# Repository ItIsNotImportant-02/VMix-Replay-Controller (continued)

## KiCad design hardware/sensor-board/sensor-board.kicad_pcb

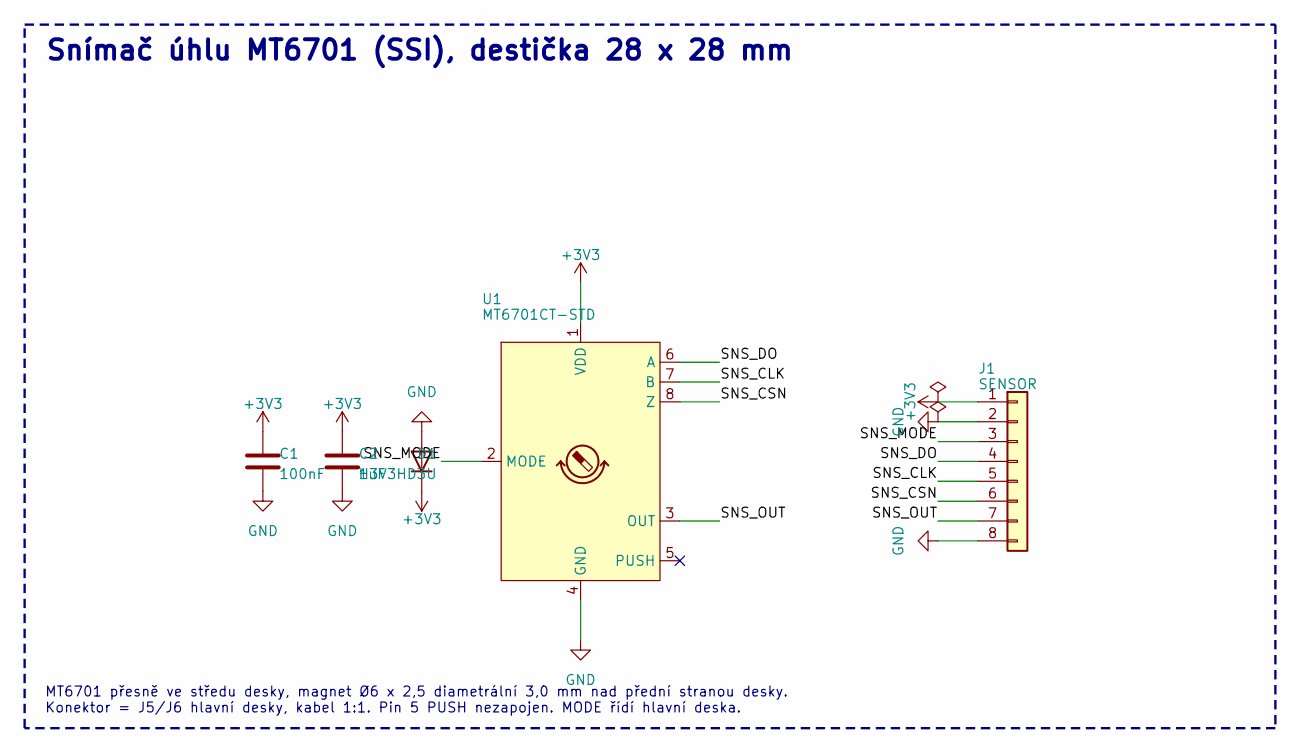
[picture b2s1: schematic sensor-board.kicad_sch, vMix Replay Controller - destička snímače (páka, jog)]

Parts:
C1: 100nF; C_0603_1608Metric; LCSC C14663
C2: 1uF; C_0603_1608Metric; LCSC C15849
D1: H3V3HD3U; D_SOD-323; MPN hongjiacheng H3V3HD3U; LCSC C20615801
J1: SENSOR; JST_PH_S8B-PH-K_1x08_P2.00mm_Horizontal; MPN S8B-PH-K-S
U1: MT6701CT-STD; SOIC-8_3.9x4.9mm_P1.27mm; MPN MT6701CT-STD-R; LCSC C3003196

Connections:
+3V3: C1.1, C2.1, D1.1 (K), J1.1, U1.1 (VDD)
/SNS_CLK: J1.5, U1.7 (B)
/SNS_CSN: J1.6, U1.8 (Z)
/SNS_DO: J1.4, U1.6 (A)
/SNS_MODE: J1.3, U1.2 (MODE)
/SNS_OUT: J1.7, U1.3 (OUT)
GND: C1.2, C2.2, D1.2 (A), J1.2, J1.8, U1.4 (GND)

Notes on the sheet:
Snímač úhlu MT6701 (SSI), destička 28 x 28 mm
MT6701 přesně ve středu desky, magnet Ø6 x 2,5 diametrální 3,0 mm nad přední stranou desky. Konektor = J5/J6 hlavní desky, kabel 1:1. Pin 5 PUSH nezapojen. MODE řídí hlavní deska.

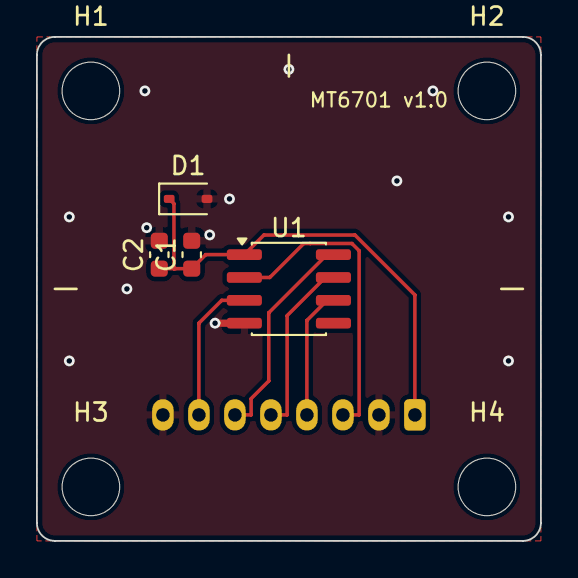
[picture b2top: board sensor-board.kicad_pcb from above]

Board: 2 copper layers, 28.0 x 28.0 mm, 9 parts (1 on the bottom side), 7 nets.

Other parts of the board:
H1, H2, H3, H4: MountingHole_3.2mm_M3

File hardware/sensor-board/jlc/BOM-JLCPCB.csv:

Comment,Designator,Footprint,LCSC Part #
100nF,C1,C_0603_1608Metric,C14663
1uF,C2,C_0603_1608Metric,C15849
H3V3HD3U,D1,D_SOD-323,C20615801
MT6701CT-STD,U1,SOIC-8_3.9x4.9mm_P1.27mm,C3003196

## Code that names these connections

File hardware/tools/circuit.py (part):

"""vMix Replay Controller main board: netlist description.

Run gen.py to turn this into KiCad schematic files. Pin assignment and design
notes are in hardware/DESIGN.md; keep both in sync.
"""
from schgen import Part
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    s.add(R("R2", "5.1k", "USB_CC2", "GND"))
    # SRV05-4 (Preferred, bez poplatku) místo USBLC6-2SC6: stejné pouzdro, 4 nezávislé diody, každá datová linka má 2
    s.add(Part("U1", "Power_Protection:SRV05-4", "SRV05-4", "Package_TO_SOT_SMD:SOT-23-6",
               pins={"1": "USB_CONN_DP", "4": "USB_CONN_DP", "3": "USB_CONN_DM", "6": "USB_CONN_DM",
                     "5": "VBUS", "2": "GND"}, lcsc="C7420376", mpn="hongjiacheng SRV05-4"))
    s.add(R("R3", "27R", "USB_CONN_DP", "USB_DP"))
    s.add(R("R4", "27R", "USB_CONN_DM", "USB_DM"))
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    # ABM8-272-T3 (doporučený v Hardware design with RP2040) má JLC skladem 1 ks (12. 11. 2026) -> náhrada se stejnou
    # zatěžovací kapacitou 10 pF, takže obvod (2x 15 pF + 1k) zůstává; ESR max 60 R místo 50 R.
    s.add(Part("Y1", "Device:Crystal_GND24", "12MHz", "Crystal:Crystal_SMD_3225-4Pin_3.2x2.5mm",
               pins={"1": "XIN", "3": "XTAL_OUT", "2": "GND", "4": "GND"}, lcsc="C5310728", mpn="TX322512M4DBDE2T",
               desc="Yajingxin 12 MHz, CL 10 pF, ESR max 60R, +-10 ppm, -30..85 C; pady 1 a 3 krystal, 2 a 4 GND"))
    s.add(R("R10", "1k", "XOUT", "XTAL_OUT"))
    s.add(C("C%d" % n, "15pF", "XIN")); n += 1      # CL 10 pF: 15/2 + ~3 pF parazitní = 10,5 pF (C0G)
    s.add(C("C%d" % n, "15pF", "XTAL_OUT")); n += 1
    s.add(Part("U4", "Memory_Flash:W25Q128JVS", "W25Q128JVSIQ", "Package_SO:SOIC-8_5.3x5.3mm_P1.27mm",
               pins={"1": "QSPI_SS", "2": "QSPI_SD1", "3": "QSPI_SD2", "4": "GND", "5": "QSPI_SD0",
                     "6": "QSPI_SCLK", "7": "QSPI_SD3", "8": "+3V3"}, lcsc="C97521"))
    s.add(C("C%d" % n, "100nF", "+3V3")); n += 1
    s.add(R("R11", "1k", "QSPI_SS", "BOOTSEL"))
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               pins={"1": "BOOTSEL", "2": "GND"}, lcsc="C318884"))
    s.add(R("R12", "10k", "+3V3", "RUN"))
    s.add(Part("SW2", "Switch:SW_Push", "RESET", "Button_Switch_SMD:SW_Push_1P1T_XKB_TS-1187A",
               pins={"1": "RUN", "2": "GND"}, lcsc="C318884"))
    s.add(R("R13", "1k", "STATUS_LED", "STATUS_LED_A"))   # žlutá Vf ~2 V -> ~1,3 mA
    s.add(Part("D3", "Device:LED", "yellow", LED0603, pins={"A": "STATUS_LED_A", "K": "GND"}, lcsc="C89811",
               mpn="NationStar NCD0603Y2"))
    s.add(Part("J2", "Connector_Generic:Conn_01x07", "DEBUG", "Connector_PinHeader_2.54mm:PinHeader_1x07_P2.54mm_Vertical",
               pins={"1": "+3V3", "2": "SWCLK", "3": "SWDIO", "4": "GND", "5": "RUN", "6": "UART_TX", "7": "UART_RX"},
               in_bom=False, desc="SWD + UART debug header (osadit ručně jen při ladění)"))
    exp = {"1": "+5V", "2": "+3V3", "3": "GND", "4": "GND", "5": "GP10", "6": "GP11", "7": "GP2", "8": "GP3",
           "9": "GP4", "10": "GP28", "15": "I2C_SDA", "16": "I2C_SCL"}
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    s = prj.sheet("Ethernet", "ethernet.kicad_sch", "W5500 + RJ45 HR911105A")
    s.note("Analogová část podle referenčního zapojení WIZnet W5500 (33R série, 49,9R terminace, 6,8nF na RX).")
    s.add(Part("U5", "Interface_Ethernet:W5500", "W5500", "Package_QFP:LQFP-48_7x7mm_P0.5mm",
               pins={"AVDD": "+3V3A", "AGND": "GND", "VDD": "+3V3", "GND": "GND", "TXN": "W_TXN", "TXP": "W_TXP",
                     "RXN": "W_RXN", "RXP": "W_RXP", "EXRES1": "W_EXRES", "VBG": None, "TOCAP": "W_TOCAP",
                     "1V2O": "W_1V2O", "RSVD": "GND", "SPDLED": None, "LINKLED": "W_LINKLED", "DUPLED": None,
                     "ACTLED": "W_ACTLED", "XI/CLKIN": "W_XI", "XO": "W_XO", "~{SCS}": "ETH_CS", "SCLK": "ETH_SCK",
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    for i in range(6):
        s.add(C("C%d" % n, "100nF", "+3V3A")); n += 1
    s.add(C("C%d" % n, "100nF", "+3V3")); n += 1
    s.add(C("C%d" % n, "4.7uF", "W_TOCAP")); n += 1
    s.add(C("C%d" % n, "10nF", "W_1V2O")); n += 1
    # EXRES1 12,4k 1 % (Basic neexistuje) = 10k + 2,4k v sérii, obě Basic 1 %
    s.add(R("R20", "10k", "W_EXRES", "W_EXRES_B"))
    s.add(R("R36", "2.4k", "W_EXRES_B", "GND"))
    s.add(Part("Y2", "Device:Crystal_GND24", "25MHz", "Crystal:Crystal_SMD_3225-4Pin_3.2x2.5mm",
               pins={"1": "W_XI", "3": "W_XO", "2": "GND", "4": "GND"}, lcsc="C9006", mpn="X322525MOB4SI (CL 12 pF)"))
    s.add(C("C%d" % n, "18pF", "W_XI")); n += 1    # CL 12 pF: 18/2 + ~3 pF = 12 pF (jako WIZ850io)
    s.add(C("C%d" % n, "18pF", "W_XO")); n += 1
    s.add(R("R21", "1M", "W_XI", "W_XO"))
    s.add(R("R22", "10k", "+3V3", "ETH_INT"))
    s.add(R("R23", "10k", "+3V3", "ETH_RST"))
    s.add(R("R35", "10k", "+3V3", "ETH_CS"))   # W5500 odpojený od SPI, dokud RP2040 nenastaví GPIO
    # TX
    s.add(R("R24", "0R", "W_TXP", "ETH_TDP"))
    s.add(R("R25", "0R", "W_TXN", "ETH_TDN"))
    s.add(R("R26", "49.9R 1%", "ETH_TDP", "+3V3A"))
    s.add(R("R27", "49.9R 1%", "ETH_TDN", "+3V3A"))
    s.add(R("R28", "10R", "+3V3A", "ETH_TCT"))
    s.add(C("C%d" % n, "22nF", "ETH_TCT")); n += 1
    # RX
    s.add(R("R29", "0R", "W_RXP", "ETH_RXP_T"))
    s.add(R("R30", "0R", "W_RXN", "ETH_RXN_T"))
    s.add(R("R31", "49.9R 1%", "ETH_RXP_T", "ETH_RCT"))
    s.add(R("R32", "49.9R 1%", "ETH_RXN_T", "ETH_RCT"))
    s.add(C("C%d" % n, "6.8nF", "ETH_RXP_T", "ETH_RDP")); n += 1
    s.add(C("C%d" % n, "6.8nF", "ETH_RXN_T", "ETH_RDN")); n += 1
    s.add(C("C%d" % n, "10nF", "ETH_RCT")); n += 1
    s.add(C("C56", "10uF", "+3V3"))   # bulk u VDD W5500 (reference WIZnet má 2x 10 uF)
    # LEDs
    # LED anody 12 a 9 na +3V3, katody 11 a 10 přes 330R do W5500 (aktivní v nule, max. 8 mA)
    s.add(R("R33", "330R", "W_LINKLED", "ETH_LINK_K"))
    s.add(R("R34", "330R", "W_ACTLED", "ETH_ACT_K"))
    s.add(Part("J4", "Connector:RJ45_Hanrun_HR911105A_Horizontal", "HR911105A", "Connector_RJ:RJ45_Hanrun_HR911105A_Horizontal",
               pins={"1": "ETH_TDP", "2": "ETH_TDN", "3": "ETH_RDP", "4": "ETH_TCT", "5": "ETH_RCT", "6": "ETH_RDN",
                     "8": "GND", "9": "+3V3", "10": "ETH_ACT_K", "11": "ETH_LINK_K", "12": "+3V3", "SH": "GND"},
               lcsc="C12074", in_bom=False, fields={"Assembly": "ruční pájení"}))
    prj.flag("+3V3A", s.name)
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    s.note("I_MAX = 58,5 x 1,3 V / R_EXT = 16,2 mA pro R_EXT 4,7k. Jas a celkový odběr omezuje firmware.\n"
           "U6 adresa 0x3C (AD=GND), U7 0x3F (AD=VCC). SDB stažený do nuly: LED po startu zhasnuté.")
    for chip, ad in (("U6", "GND"), ("U7", "+5V_LED")):
        pins = {"VCC": "+5V_LED", "GND": "GND", "EP": "GND", "SDA": "I2C_SDA", "SCL": "I2C_SCL",
                "~{SDB}": "LED_SDB", "AD": ad, "R_EXT": "%s_REXT" % chip}
        for k in range(1, 37):
            pins["OUT%d" % k] = None
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    s = prj.sheet("Inputs", "inputs.kicad_sch", "2x TCA9555 expandér")
    s.note("U8 adresa 0x20, U9 0x21. INT (open drain) společný, pull-up R50.")
    for chip, a0 in (("U8", "GND"), ("U9", "+3V3")):
        pins = {"VCC": "+3V3", "GND": "GND", "EPAD": "GND", "SCL": "I2C_SCL", "SDA": "I2C_SDA",
                "~{INT}": "BTN_INT", "A0": a0, "A1": "GND", "A2": "GND"}
        for name, (c, port) in TCA_MAP.items():
            if c == chip:
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
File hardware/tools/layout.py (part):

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    b.term("R7", "2", 0)
    x6, y6, _ = b.pin("R6", "2")
    b.wire((x6, y6 + 1), (x6 + 3, y6 + 1))
    b.label("VSENSE_5V", x6 + 3, y6 + 1, "right")
    d.shunt("C8", *b.P(x6 + 2, y6 + 1), "down", L=g(1))
    # test points
    for i, ref in enumerate(("TP1", "TP2", "TP3", "TP4", "TP5", "TP6", "TP7")):
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    for k in range(30):
        name = "GPIO%d" % k if k < 26 else "GPIO%d/ADC%d" % (k, k - 26)
        b.term(U, name, 2)
    # crystal: XIN/XOUT labels, R10 in series, Y1 with load caps (bottom-left)
    b.term(U, "XIN", 2)
    b.term(U, "XOUT", 2)
    b.h2("R10", 9, 50)
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    b.wire((rx, ry), (rx, ry + 1), (rx + 3, ry + 1))
    b.junction(rx, ry + 1)
    b.wire((rx, ry + 1), (rx - 3, ry + 1))
    b.label("RUN", rx - 3, ry + 1, "left")
    d._mark("R12", "2")
    b.place("SW2", rx + 5, ry + 1, 0, ref_at=(rx + 3, ry - 1.5), val_at=(rx + 3, ry + 3.5))
    sx, sy, _ = b.pin("SW2", "2")
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    for r in ("R31", "R32"):
        b.to_point(r, b.side(r, "right"), gx + 6, gy + 10)
    b.wire((gx + 6, gy + 10), (gx + 8, gy + 10))
    b.label("ETH_RCT", gx + 8, gy + 10, "right")
    b.h2("C53", gx + 3, gy + 14)
    b.h2("C54", gx + 3, gy + 17)
    b.place("R28", gx + 3, gy + 21, 90)
    b.term("R28", b.side("R28", "left"), 0)
    rx, ry, _ = b.pin("R28", b.side("R28", "right"))
    b.wire((rx, ry), (rx + 3, ry))
    b.label("ETH_TCT", rx + 3, ry, "right")
    d._mark("R28", b.side("R28", "right"))
    d.shunt("C52", *b.P(rx + 1, ry), "down", L=g(1))
    b.v2("C55", gx + 14, gy + 23, Lt=1)
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
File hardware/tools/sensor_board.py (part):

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    from schgen import Part
    P = []
    P.append(Part("U1", "Sensor_Magnetic:MT6701CT", "MT6701CT-STD", "Package_SO:SOIC-8_3.9x4.9mm_P1.27mm",
                  pins={"1": "+3V3", "2": "SNS_MODE", "3": "SNS_OUT", "4": "GND",
                        "6": "SNS_DO", "7": "SNS_CLK", "8": "SNS_CSN"},
                  lcsc=LCSC["MT6701"], mpn="MT6701CT-STD-R"))
    P.append(Part("C1", "Device:C", "100nF", "Capacitor_SMD:C_0603_1608Metric", pins={"1": "+3V3", "2": "GND"},
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    P.append(Part("D1", "Device:D", "H3V3HD3U", "Diode_SMD:D_SOD-323", pins={"1": "+3V3", "2": "GND"},
                  lcsc=LCSC["TVS"], mpn="hongjiacheng H3V3HD3U", desc="ESD/TVS 3.3 V unidirectional, Preferred"))
    P.append(Part("J1", "Connector_Generic:Conn_01x08", "SENSOR", "Connector_JST:JST_PH_S8B-PH-K_1x08_P2.00mm_Horizontal",
                  pins={"1": "+3V3", "2": "GND", "3": "SNS_MODE", "4": "SNS_DO", "5": "SNS_CLK", "6": "SNS_CSN",
                        "7": "SNS_OUT", "8": "GND"},
                  mpn="S8B-PH-K-S", in_bom=False, fields={"Assembly": "ruční pájení"}))
    return {p.ref: p for p in P}
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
